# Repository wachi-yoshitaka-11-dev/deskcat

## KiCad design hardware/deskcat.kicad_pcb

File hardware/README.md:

# ハードウェア設計データ

このディレクトリは編集可能な図面を置く。型番、GPIO、抵抗値、電源条件、安全制限、実験結果の正本は [`docs/hardware/`](../docs/hardware/README.md) にある。**配線を変える PR は、同じ PR で KiCad 回路図とブレッドボード配線図も更新する。** 実験記録の `Wiring revision` の行を変えて配線図を更新しない PR は、`scripts/check_wiring_figure_sync.py` が CI で落とす（図に関係しない場合の宣言は [CONTRIBUTING](../CONTRIBUTING.md) の「ハードウェア実験」）。 **図は最終的な配線を描く。測定のためだけの一時配線は描かず、`Wiring-Figure: not-applicable <理由>` で通す。** 図は 3 つ（`breadboard/layout.svg`、`universal-board/` の電源の基板の図、`overview/layout.svg`）である。電源の基板の図は計画で、[#405](https://github.com/wachi-yoshitaka-11-dev/deskcat/issues/405) で付けた後に現物と照合して完成図にする。`overview/layout.svg` は最終形のつながりを回路図の netlist から生成する。この検査は配線図の更新だけを要求する。穴位置や線色の変更は論理回路を変えないためで、論理接続が変わる場合の KiCad 回路図の更新は人が行う。 図と正本が食い違う場合は変更を止めて照合する。

| データ | 対象と状態 |
| --- | --- |
| [`deskcat.kicad_pro`](deskcat.kicad_pro)、[`deskcat.kicad_sch`](deskcat.kicad_sch) | #512 の論理回路。EXP-019 測定前の基準配線に、EXP-022 の UART と EXP-025 の LED 2枝を加えた設計上の合成図。抵抗の `Value` は数値の代わりに値の正本文書名を示す（値の正本が無い `R19` だけは、現在組んである値を出所の EXP-028 とともに書く。設計値ではない）。2026-11-15 に、`PROTO-02` の電源の経路（入力 → 端子台 → PTC → MOSFET → 分岐点 → servo・Pi・logic の枝。未実装の計画）を同じ図に足した。pin 番号の出所は下の`回路図の pin 番号`。KiCad 8.0.9 の `kicad-cli` で読み込み、ERC を実行した（下の`KiCad の ERC`）。 |
| [`universal-board/`](universal-board/plan.md)、[`deskcat.kicad_pcb`](deskcat.kicad_pcb) | `PROTO-02`（電源の基板）の**実装の計画（未実装）**。どの穴にどの部品をどの向きで挿し、どこをはんだでつなぎ、どの線をどこへ出すか。**正本は KiCad の基板ファイル `deskcat.kicad_pcb`**（回路図と同じ project）。図 `plan-front.svg`・`plan-back.svg` は KiCad から書き出した派生物で、`plan.md` は凡例・向き・測る所である。見た目の図 `view-front.svg`・`view-back.svg`（部品面とはんだ面）は、基板ファイルから `universal-board/render_view.py` が書く派生物である（寸法の正本ではない。資料に無いものは破線または注記で `TBD`）。GND の star point の規則は `check_star_point.py` が基板ファイルを読んで確かめる。**完成図ではない。**#405 のはんだ付けはこの計画に従い、付けた後に現物と照合して完成図にする。 |
| [`overview/`](overview/wiring-table.md) | 最終形の全体の配線（ブレッドボード B1・B2・B3、`PROTO-02`、Pi、サーボ、LCD、M-12001）のつながり。位置は胴の中の位置関係だけで、寸法は表さない。`generate.py` が回路図から書き出した netlist（`deskcat-netlist.xml`）を入力にして `layout.svg` と `wiring-table.md` を生成し、図の線と netlist が合うことを検査する。板どうしの線はブレッドボードの `breadboard-rebuild/generate.py` のデータを読み込む。#18 の試験だけの物（端子台S、PSU、試験用の負荷、shunt）は描かない。 |
| [`breadboard/layout.svg`](breadboard/layout.svg) | 最終の配線の図。2026-10-31（EXP-052）に、組み直した後の配置（`breadboard-rebuild/layout.svg`）で置き換えた。測定のためだけの一時配線（EXP-030〜035 の Arduino・分圧・シャント・測定用の戻り線）は描かない。柔らかい線の色と穴は `breadboard-rebuild/wiring-table.md` が正である。組み直す前の図は Git の履歴にある。 |
| [`breadboard-rebuild/`](breadboard-rebuild/README.md) | #512 の組み直しの配置（2026-10-31 に組んだ。EXP-052）。配置図 `layout.svg` と結線表 `wiring-table.md` は `generate.py` のデータから生成する。組み直した後のこの配置で、上の図を置き換えた。組み直す前の図は Git の履歴にある。 |
| [`bench-18/`](bench-18/wiring-table.md) | #18 の窓と段1の servo 電源の経路（`PSU-BENCH-01` → 端子台 A・B・S → `MF-R135` → シャント → jumper wire → (D)・(B) の負荷／段1の servo の plug）の bench の図。正本は `generate.py` のデータで、結線表 `wiring-table.md`（節点の表）と `layout.svg` はそこから生成する。**#405 の図とは別物で、`breadboard/layout.svg` は置き換えない。**`MEAS-02` の線は測定のためだけの一時配線なので描かない。 |
| [`wokwi/esp32-boot-pulls/diagram.json`](wokwi/esp32-boot-pulls/diagram.json) | 起動時 GPIO と外部 pull の初期評価用。ESP32、pull、LED の枝、ILI9341 互換表示部だけを配置した。全機器をシミュレーションした構成ではない。 |

基準図①は、ユーザーの配線地図と回答から AI が作り、ユーザーが照合した版である。SVG 本文の SHA-256 は末尾改行を除いて `a91e6d1e669258f477fcde5e0d77fda64260d6a0d322a3c12491654c39a985fa` と一致した。基準時点は EXP-019 の測定前で、測定のためだけに抵抗やジャンパを挿した状態は含めない。EXP-021・EXP-022 は `ACCEL-01`、`ENV-01`、`DISP-01` の配線が戻した状態から変わっていないと記録する。Pi の給電差し替え（EXP-020、EXP-023）は USB 端子側であり、ブレッドボードの変更ではない。

#512 コメントの `RES-PULL-01` と `HW-TBD-032` の食い違いは、現行の [Hardware BOM](../docs/hardware/hardware-bom.md) と [TBD Register](../docs/hardware/tbd-register.md) を照合した。BOM は後の改訂で、当初の4本に `LCD-BL` の1本を加えた確定5本と実装済みの状態を記録している。`HW-TBD-032` も close 済みである。BOM の「計4本」は当初の選定経緯を指し、現行の総数ではない。GPIO Assignment に残っていた `LCD-CS`／`LCD-RST` の古い状態説明を、2026-09-07 の `EXP-011` と照合して訂正した。

EXP-022 の UART は [GPIO Assignment](../docs/hardware/gpio-assignment.md) の GPIO と接続条件、および [実験記録](../docs/hardware/experiment-log.md) に従う。抵抗の位置は EXP-022 が「紫の線（Pi の pin 8、GPIO14 `TXD`）に `h1`–`h4`、青の線（pin 10、GPIO15 `RXD`）に `i2`–`i5`、各線に 4.7 kΩ が1本」と記録している。抵抗の両端につながる線の穴位置は記録に無く TBD である。GND は Pi pin 39 と ESP32 の J3 の GND を結ぶ。UART 信号線を接続してよい条件は正本を毎回参照する。

EXP-025 の [LED デモ回路](../docs/hardware/led-514-demo.md)は GPIO → 電流制限抵抗 → LED アノード → カソード → GND、GPIO → pull-down → GND の2枝である。GND rail の導通はユーザー申告で、実測されていない。EXP-025 の点灯試験中は UART 信号線の ESP32 側を外した。[EXP-026](../docs/hardware/experiment-log.md)では LED の GPIO 線を外している。この合成図を、UART と LED を同時に接続・通電して検証した証拠として使わない。

## 設計データの層と、このディレクトリのファイル

電子回路の設計データは、論理（何と何がつながるか）、物理（どこに置き、どこをはんだでつなぐか）、部品の定義、製造の4つの層に分かれ、論理から物理へ写して作る。DeskCat の今の構成（ブレッドボードと、既製のユニバーサル基板1枚）で要るものと、そのファイルは次のとおりである。

| 層 | データ | このリポジトリ | 状態 |
|---|---|---|---|
| 論理 | 回路図 | [`deskcat.kicad_sch`](deskcat.kicad_sch)（信号の側と、`PROTO-02` の電源の経路） | あり。LCD の VCC は決めていない（段階C では DISP-01 を使わない。今の構成の 3V3 pin 給電・J1 開放は #461 の承認範囲で、段階Cへ広げない。最終の VCC は #405 の見直しで決める。`PROTO-02` の配線には効かない）。ESP32 の 5 V 入力は案B（`J8`、ユーザーの決定 2026-11-23）で決めた |
| 論理 | netlist（どの部品のどの pin がどの節点か） | 回路図から `kicad-cli sch export netlist` で出し、[`overview/deskcat-netlist.xml`](overview/deskcat-netlist.xml) に置く（overview の図の入力。回路図を変えたら書き出し直す）。基板ファイルとの照合は KiCad の DRC（`--schematic-parity`）が行う | 回路図から出せる |
| 物理 | 試作のブレッドボードの配線 | [`breadboard/layout.svg`](breadboard/layout.svg)、[`breadboard-rebuild/wiring-table.md`](breadboard-rebuild/wiring-table.md) | あり（2026-10-31 の組み直し） |
| 物理 | 試作の端子台の配線（#18 の bench） | [`bench-18/`](bench-18/wiring-table.md) | あり。#18 の試験の間だけの配線 |
| 物理 | はんだ付けする基板の実装図 | KiCad の基板ファイル [`deskcat.kicad_pcb`](deskcat.kicad_pcb)（計画）と、書き出した図・凡例の [`universal-board/`](universal-board/plan.md) → 照合後に完成図（#405） | 計画あり。DRC（回路図との照合を含む）で違反 0 |
| 物理 | 全体の配線（基板どうしと胴の中） | [`overview/layout.svg`](overview/layout.svg)、[`overview/wiring-table.md`](overview/wiring-table.md) | あり。回路図から書き出した netlist（`overview/deskcat-netlist.xml`）から `overview/generate.py` で生成し、netlist と図の線が合うことを検査する |
| 部品の定義 | symbol（回路図の記号） | project の library [`DeskCat.kicad_sym`](DeskCat.kicad_sym)（`sym-lib-table`）。抵抗は KiCad 標準の `Device` | あり |
| 部品の定義 | footprint（はんだ付けする足の位置と形） | project の library [`DeskCat.pretty/`](DeskCat.pretty)（`fp-lib-table`）。`PROTO-02` に載る部品だけ | あり。寸法の出所は [`universal-board/plan.md`](universal-board/plan.md) |
| 部品の定義 | SPICE のモデル | 無い | 要らない。起動時の pull の解析に具体的な課題が無い（#512 の本文） |
| 製造 | BOM（部品表） | [`docs/hardware/hardware-bom.md`](../docs/hardware/hardware-bom.md) | あり（手編集の正本は1つ） |
| 製造 | Gerber・drill・Pick & Place・3D（STEP） | 無い | 要らない。工場で基板を作らず、筐体との寸法連携は #34・#405 の現物合わせで行う（#512 の本文）。必要になれば基板ファイルから KiCad で出せる |

**論理と物理のつながり：**回路図・基板ファイル・部品の library は1つの KiCad project（`deskcat.kicad_pro`）である。基板の部品の参照番号（`J5`〜`J8`、`F1`、`Q1`、`R18`、`R20`、`C1`・`C2`、`W1`）と節点は回路図から来ており、`kicad-cli pcb drc --schematic-parity hardware/deskcat.kicad_pcb` が食い違いを検出する。#512 の本文は「専用 PCB の `.kicad_pcb` は成果物に含めない」としている。ここでの `.kicad_pcb` は既製のユニバーサル基板の上の配置の計画であり、工場へ出す基板ではない（Gerber 等は作らない）。データの形式を業界標準の KiCad に揃えるために使う。KiCad の個人設定（`*.kicad_prl`）とバックアップは [`.gitignore`](.gitignore) で Git に入れない。

## 回路図の pin 番号

- `MCU-01` の header 番号（`J2-*`・`J3-*`）は、[GPIO Assignment](../docs/hardware/gpio-assignment.md) の`公式回路図revision`行（Espressif の ESP32-DevKitC V4 公式回路図と、現物の silk の照合）による。`GPIO34`（`TOUCH-IRQ`）の `J2-5` は、同行の左列の5番目が `34` であることと、公式回路図（`esp32_devkitc_v4-sch.pdf`、sha256 `92961687b5fac64b8870ddc2f5e8528351e515b6cafd49e7d1bba4fb974a7349`）の `J2` の pin 5 が `IO34` であることの両方で確かめた（2026-11-15）。
- `ENV-01` の pin 番号 1〜6 は、[AE-BME280 製品説明書](https://akizukidenshi.com/goodsaffix/AE-BME280_manu_v1.1.pdf)（v1.1、sha256 `903c2e49064f279ff2738391ca6beb24a70a3d91a4e2118621381faef66a1e76`）の`ピン番号と機能`（1 `VDD`、2 `GND`、3 `CSB`、4 `SDI`、5 `SDO`、6 `SCK`）による。pin 3（`CSB`）は module の上の `J3` で `VDD` へつなぐため、回路図では線を引いていない（netlist では未接続の pin になる）。
- `ACCEL-01`（秋月 M-06724）は、製造元の pin 番号が無い。商品ページは 404 で、module の資料が無い（[Sensor Datasheet Notes](../docs/hardware/sensor-datasheet-notes.md) の`module boardの値（秋月 M-06724）`）。**回路図の pin 番号には、header の silk の表記（`Vs`、`GND`、`SCL`、`SDA`、`CS`、`SDO`、`INT1`、`INT2`、`VDD`）をそのまま使った。**silk の表記は module の上で1つずつ違うので、どの端子かは一意に決まる。header の並び順に番号を振ることはしない（端からの順序の資料が無い）。

## KiCad の ERC

2026-11-23（最初の実行は 2026-11-16）、KiCad 8.0.9 の `kicad-cli` で回路図を読み込み、ERC を実行した（環境は [Version Record](../docs/toolchains/version-records/2026-11-23-kicad-pcb-native-linux.md)。native Linux の KiCad 8.0.9。最初の実行は [2026-11-15 の VM](../docs/toolchains/version-records/2026-11-15-kicad-erc-vm.md)）。**Errors 0、Warnings 168** である（電源の経路、サーボ信号の直列抵抗 R19、project の library を足し、機能ごとの配置に描き直し、`PROTO-02` の shunt `R20`・bulk capacitor `C1`・`C2`・`ADC-SHUNT` の出口 `W1`・`J8` の経路を足した後）。警告の内訳は、pin と wire の端が接続の grid の外にある（`endpoint_off_grid`）148件と、抵抗の記号の KiCad 標準 library `Device` が実行した環境（native Linux の KiCad 8.0.9。`/usr/share/kicad` に `symbols` が無い）に入っていない（`lib_symbol_issues`、記号は回路図に埋め込み済み）20件で、どちらも接続を変えるものではない。netlist を出力し、`MCU-01` の各 pin の net が上の header 番号と [GPIO Assignment](../docs/hardware/gpio-assignment.md) の GPIO に合うこと、`ACCEL-01` の `SDO` と `ENV-01` の `SDO` が GND（address `0x53` と `0x76`。EXP-065 の起動 log の `accel=0x53 env=0x76`）にあることを確かめた。

基板ファイルの DRC（`kicad-cli pcb drc --schematic-parity --severity-all`）は、違反 0、未接続 0、回路図との食い違い 0 だった。

**この ERC が保証しないこと：**symbol の pin はすべて passive なので、出力どうしの衝突のような pin の種別の検査は効かない。GUI の窓での表示は確かめていない（ERC を実行した native Linux の環境に `DISPLAY` が無いため）。作業セッション（AI）が `kicad-cli sch export pdf` で描画して画像にし、確かめた（下の`閉じた項目`）。**人は見ていない。**

## Wokwi と物理図の評価

[Wokwi の diagram.json 形式](https://docs.wokwi.com/diagram-format)は JSON で部品と pin 間の接続を編集できる。抵抗の `value` 属性には数値が必須であり、[GPIO Assignment](../docs/hardware/gpio-assignment.md) と [LED デモ回路](../docs/hardware/led-514-demo.md)を写した値を入れている。値の変更時は正本と同じ PR で照合する。[Wokwi の抵抗モデル](https://docs.wokwi.com/parts/wokwi-resistor)は簡易的なアナログモデルで、起動時の pull を配置できても実機の起動挙動は立証できない。

**ブラウザで試した結果（2026-11-15）。**ログインせずに `wokwi.com` の新しい ESP32 project を開き、`diagram.json` を貼り替え、sketch を「外部 pull のある pin を入力にして読み、serial へ出す」ものに替えて simulation を始めた。project は保存していない（保存にはログインが要る）。API トークンは使っていない。**この試行を誰が行い、誰が画面を見たかの記録は無い**（記録の出所の PR #769 は「ブラウザから試した」と書くだけで、主語が無い）。

- 表示：`diagram.json` を読み込み、ESP32・抵抗・LCD と線が描かれた（画面に入った範囲を確かめたとの記録がある。誰が見たかの記録は無い）。
- 起動：ROM の log は `rst:0x1 (POWERON_RESET),boot:0x13 (SPI_FAST_FLASH_BOOT)` で、sketch まで進んだ。読んだ値は、pull-down の GPIO2・4・5・27 が 0、pull-up の GPIO16・21・22・25・26 が 1 で、図の pull の向きと合った。
- **boot mode は再現されない。**`GPIO0` を GND へ直結する線を足して起動し直すと、sketch は `GPIO0=0` を読んだが、ROM の log は同じ `boot:0x13 (SPI_FAST_FLASH_BOOT)` のままだった（download mode に入らない）。Wokwi は strapping pin の電圧から boot mode を決めていない。実機の起動 log は `boot:0x12`（EXP-052）で、値も一致しない。
- したがって Wokwi で言えるのは「外部 pull の論理接続を、起動後に入力として読むと図の向きになる」ことまでで、strapping pin の起動挙動は確かめられない。

Wokwi の [ILI9341 部品](https://docs.wokwi.com/parts/wokwi-ili9341)では RST と backlight はシミュレーションされない。`DISP-01` の touch は XPT2046 だが同部品の touch とは一致しない。Wokwi の汎用 LED も `LED-COMM-01`／`LED-REACT-01` の電気特性を保証するモデルではない。`ACCEL-01` の ADXL345、`ENV-01` の BME280、Pi Zero W の UART、ブレッドボードの実際の穴位置は、この評価構成にモデル化していない。外部 pull の論理接続には Wokwi を使い、実際の穴位置には SVG を使う。同じ回路を Wokwi と Fritzing で二重に手編集しない。

**カスタムチップ（2026-11-22 に公式文書を読んだ）。**[Getting Started](https://docs.wokwi.com/chips-api/getting-started)は、Custom Chips API で「新しい simulation model を作り、センサー、表示器、メモリなどを作れる」と述べ、chip は C（または WebAssembly にコンパイルできる言語）で書き、**API は beta** だと注記する。[I2C API](https://docs.wokwi.com/chips-api/i2c)は、`i2c_init` に SCL・SDA の pin、7 ビットの I2C アドレス、connect・read・write・disconnect の callback を渡して I2C の device を作ると述べる。したがって、`ACCEL-01`（ADXL345）と `ENV-01`（BME280）を、アドレスと register の読み書きを返す I2C の chip として**書くこと自体は、公式の記述の範囲でできる**。**作らない。**理由は3つである。(1) 作った chip が返す値は、datasheet から起こした自作の model であり、実物の挙動を保証しない。DeskCat の firmware の driver がその model で動いても、実物のセンサーで動く根拠にならない。(2) Wokwi は外部 pull の論理接続の評価にだけ使うと決めた（下の採否）。外部 pull の評価に I2C のセンサーは要らない。(3) Wokwi で確かめられない起動挙動と電源・安全は、chip を足しても確かめられない（上）。**確かめていない：**この2ページに、ADXL345 や BME280 の既製の chip の有無の記述は無い（標準部品の一覧は、[#512 の本文](https://github.com/wachi-yoshitaka-11-dev/deskcat/issues/512)にある 2026-09-30 の確認のまま）。自作した chip の保存や共有に、ログインが要るかどうかも確かめていない。

### 採否（2026-11-15）

| 観点 | Wokwi | Fritzing | KiCad と、生成した SVG |
|---|---|---|---|
| 必要な配線の表現 | ESP32・抵抗・LED・ILI9341 の論理接続は表せる。`ACCEL-01`・`ENV-01`・XPT2046 は標準部品に無い。strapping の起動挙動は再現されない（上） | ブレッドボードの穴と部品の形は表せるが、`ACCEL-01`（M-06724）・`ENV-01`（AE-BME280）・`DISP-01`（MSP2807）・端子台 `114217` の部品図は、実物に合うものを作るか探して端子対応とライセンスを確かめる必要がある | 回路図と `PROTO-02` は KiCad。ブレッドボードの穴と線の色（`breadboard-rebuild/`）と bench の節点（`bench-18/`）は、Python のデータから生成した SVG と結線表 |
| 実物との端子対応 | 部品の pin 名は Wokwi の model の名前で、実物の silk とは別。DevKitC V4 の `GND.1` のような名前を写し替える | 部品図ごとに作る必要がある（上） | 一次資料と現物の silk の名前を、記号・footprint・データにそのまま書いている |
| 編集・保存のしやすさ | JSON を Git で差分にできる。ブラウザでの保存はログインが要る（試していない） | `.fzz` は zip の binary で、差分を読めない。この VM には入っていない | KiCad の file は文字の S 式で、Git で差分を読める。ブレッドボードの SVG は生成と検査を `--check` で機械で回せる |

**Wokwi は、外部 pull の論理接続の評価構成としてだけ使い続ける**（`esp32-boot-pulls/` のまま広げない）。起動の安全の確認には使わない。**Fritzing は採らない。**実物（秋月の module・端子台）に合う部品図を探すか作り、端子対応とライセンスを確かめる手間が要り、それでも `.fzz` は差分を読めない。`PROTO-02` は KiCad で、ブレッドボードは生成した SVG で表せている。Fritzing の部品 library に実物に合う図があるかは、この判断では探していない。`hardware/deskcat.fzz` と `hardware/fritzing/` は作らない。ブレッドボードの図と KiCad の回路図との接続差分は、結線表（`wiring-table.md`）と netlist を照らして見る。

## 残っている TBD と、閉じた項目

- `PROTO-02` の現物：計画（[`universal-board/plan.md`](universal-board/plan.md)）は描いた。**はんだ付けの後に現物と照合して完成図にする作業は #405 の範囲で、追跡を #405 へ移した**（#405 の受け入れ条件に、計画図に従ったはんだ付けと、現物との照合・完成図の記録の項目がある）。**基板の未実装状態を完成図として描かない。**計画の`測る所`（M1〜M8。M1・M3・M5 は決めて閉じた）は、#512 の受け入れ条件の「表現できない部分と `TBD` を列挙する」に当たる列挙として `plan.md` に残す。測る作業も #405 側で行い、まだ測っていない。
- **LCD の信号線と touch の線（2026-10-31 の組み直し後）：**導通は電源2本と短絡だけを測った（EXP-052）。`CS`・`DC`・`SDI`・`SCK`・`LED` は、組み直し後の製品 build で LCD が描かれた記録（EXP-062 など）で動作を確かめた。**`RESET`（`display.rs` は SWRESET を送るので、描画だけでは線の有無を断定できない）、`SDO`（製品 build は読まない）、`T_DO`・`T_CS`（組み直し後の窓で使った build は touch を読まない `no-touch-487`。既定の製品 build は読む）、`T_IRQ`（製品 build は既定も `no-touch-487` も読まない。`touch.rs`）は、組み直し後の確認が無い。**#512 の受け入れ条件は導通の実測を求めておらず、LCD の touch を使う作業が出たとき、その作業の窓で1本ずつ確かめる。
- **`TBD`**（`overview/wiring-table.md` の T1〜T3 と `universal-board/plan.md` の `未決の一覧`）：ESP32 の 5 V 入力（`J8`）は案B に決めた（ユーザーの決定、2026-11-23。記録は power-budget.md の`ESP32の給電経路`節）。サーボの plug とのつなぎ方（T1）は #405 が持つ。J8 の枝（P7・X5）の線とつなぎの部材と、案Bで 5V-NODE に載る B1 の上の要素（`J2-19` の列の接点、ADC-5V の分圧の上の抵抗（回路図の R8、B1 の配線表の R11）とその接点・線）の扱い（T3）も #405 が持ち、決まるまで J8 から ESP32 へ給電しない（案Bの条件は power-budget.md の`案Bを採る条件`の行が持つ）。LCD の VCC（T2）は決めていない（段階C では DISP-01 を使わない。今の構成の 3V3 pin 給電・J1 開放は #461 の承認範囲で、段階Cへ広げない。最終の VCC は、`HW-TBD-024`・`HW-TBD-025`(a) と回路図の版の一致が揃えば #405 の見直しで決める）。台帳の [`HW-TBD-024`](../docs/hardware/tbd-register.md#hw-tbd-024) は、LCD が耐えられる電流の上限の項目で、電圧の項目ではない。

### 閉じた項目

- **回路図の `R19`（サーボ信号の直列抵抗）の値：現在組んである値として記入した。**値は回路図の `Value` が持つ（ここへ写さない）。出所は [EXP-028](../docs/hardware/experiment-log.md#exp-028-sg90の初回のサーボ動作の試み測定用buildジャンパー線の接続2回試みた) の記録で、ブレッドボードでは [`breadboard-rebuild/wiring-table.md`](breadboard-rebuild/wiring-table.md) の `R6` にあたる。**これは設計値の正本ではない。**値を決める正本が無いまま、現物に合わせて図へ書いたものである。図は実機の電源・安全確認の代わりにならない。
- **回路図の KiCad での表示（2026-11-22）：** 作業セッション（AI）が `kicad-cli sch export pdf` で回路図を描画し、画像にして確かめた。**人は見ていない。**画像で、回路図の全体（枝ごとの配置・label・注記）が描かれることと、`R19` の `Value` が隣の `R7`・`R8` の文字に重なっていること（初稿の長い `Value`。短くして直した）を確かめた。**GUI の窓（`eeschema`）は起動していない。**この端末に画面が無い（`DISPLAY` が空）ためで、描画は同じ KiCad 8.0.9 の plot の経路による。受け入れ条件の「対応するツールで開け」は、読み込み・ERC（上の`KiCad の ERC`）・この描画で満たすと扱う。
- **`ENV-01` の `CSB`–`VDD` はんだジャンパ `J3` の導通：測らずに閉じた（2026-11-15）。**根拠は次の3つである。
  1. [EXP-014](../docs/hardware/experiment-log.md#exp-014-env-01bme280のj3はんだジャンパの実施記録)：`J3` ははんだ付け済み（2026-09-07）。確認の方法は写真とテスターである（申告の記録）。**測定値は無い。**
  2. EXP-052 の起動で `env_chip_id raw=0x60`（BME280）が読め、EXP-065 の起動 log は `env=0x76`、温湿度は Pi へ1分ごとに送られた。**これは `J3` の導通を測ったことではない。**言えるのは「それらの起動のたびに、`CSB` が `VDD` の側にあった」ことである。BME280 は `CSB` が `VDDIO` につながると I2C、一度 low に引かれると次の power-on-reset まで I2C を止める（Bosch BME280 Data Sheet、`BST-BME280-DS001-24`、Revision 1.24 の 6.1 `Interface selection`）。`J3` の抵抗値や、はんだの状態は分からない。
  3. `J3` は安全要件の5項目に効かない（[Hardware Safety Policy](../docs/governance/hardware-safety-policy.md)）。`J3` が切れて起きるのは I2C で `ENV-01` が応答しなくなることで、電源・servo の安全制限には関わらない。
- Wokwi のブラウザ表示と起動時の挙動、KiCad でのファイル読み込みと ERC（上の各節）。

写真と地図の画像は Git に入れない。大きな製造用生成物、vendor binary、第三者文書も追跡方法とライセンスを決めずに追加しない。

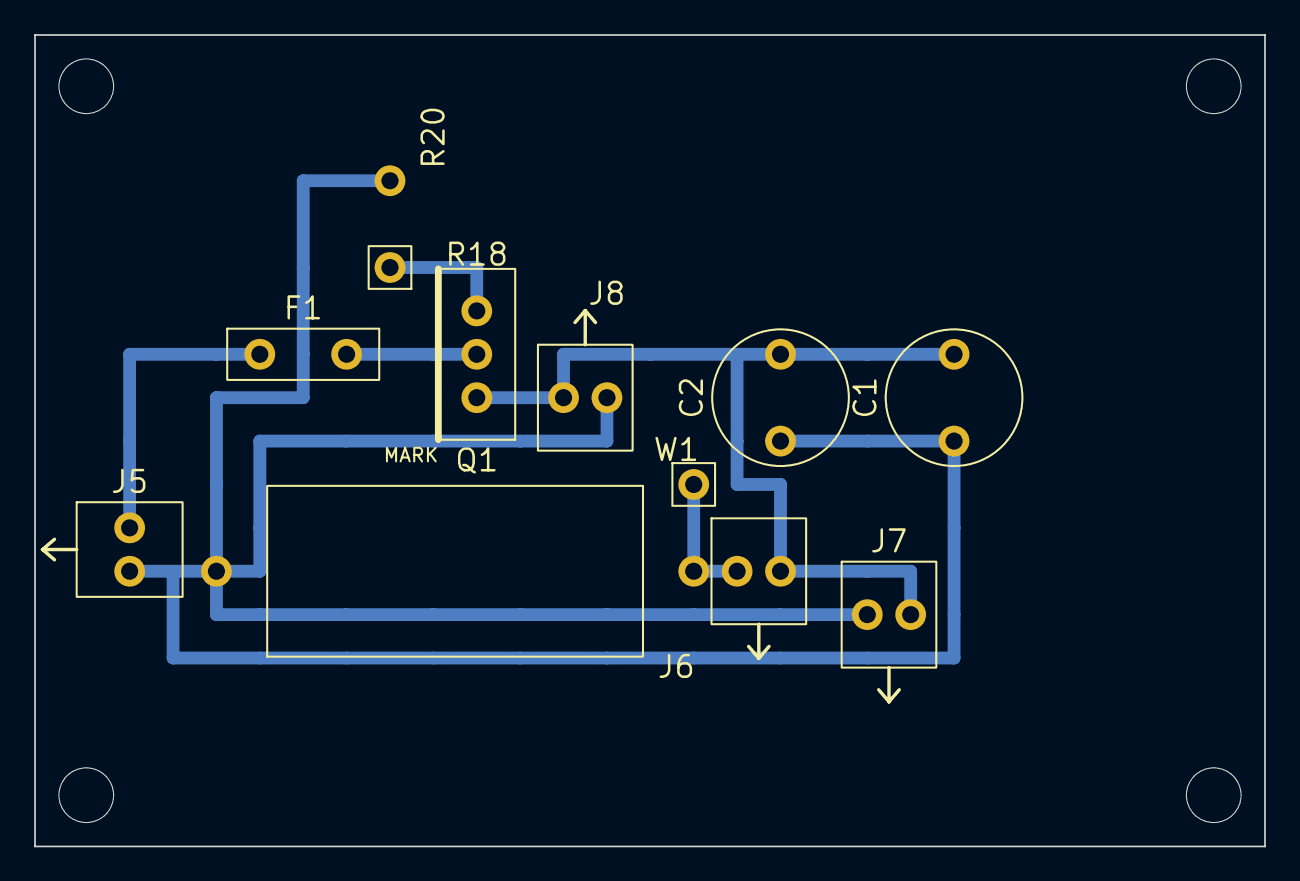
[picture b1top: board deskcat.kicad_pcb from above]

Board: 2 copper layers, 72.0 x 47.5 mm, 15 parts (0 on the bottom side), 6 nets.

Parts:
C1, C2: 470 µF／16 V（g108426。power-budget.md。2 個分の穴。3 個目が要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; C_Radial_D8_P5.08
F1: PROT_OC_01_MF_R135; PTC_MF-R135_Radial_P5.08
H1, H2, H3, H4: MountingHole; MountingHole_3.2mm
J5: TB_114217; TB_114217_WireLeft
J6, J7: TB_114217; TB_114217_WireLid
J8: TB_114217; TB_114217_WireFloor
Q1: PROT_RP_01_2SJ334; 2SJ334_SC-67_Vertical_MarkRight
R18: power-budget.md 10k gate; R_Vertical_P5.08
R20: 0.1 Ω 5 W（MEAS-01。SQP5WJ0R1B。power-budget.md GND 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; SHUNT_SQP5W_Lying_P27.94
W1: ADC-SHUNT の線の出口（B1 GPIO32 へ）; WireExit_1.0

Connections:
/5V-IN: F1.a, J5.+
/5V-NODE: C1.+, C2.+, J6.+, J7.+, J8.+, Q1.3
/5V-PTC: F1.b, Q1.2
/ADC-SHUNT: J6.-, R20.1, W1.1
/GND: C1.-, C2.-, J5.-, J7.-, J8.-, R18.2, R20.2
/Q1-GATE: Q1.1, R18.1
